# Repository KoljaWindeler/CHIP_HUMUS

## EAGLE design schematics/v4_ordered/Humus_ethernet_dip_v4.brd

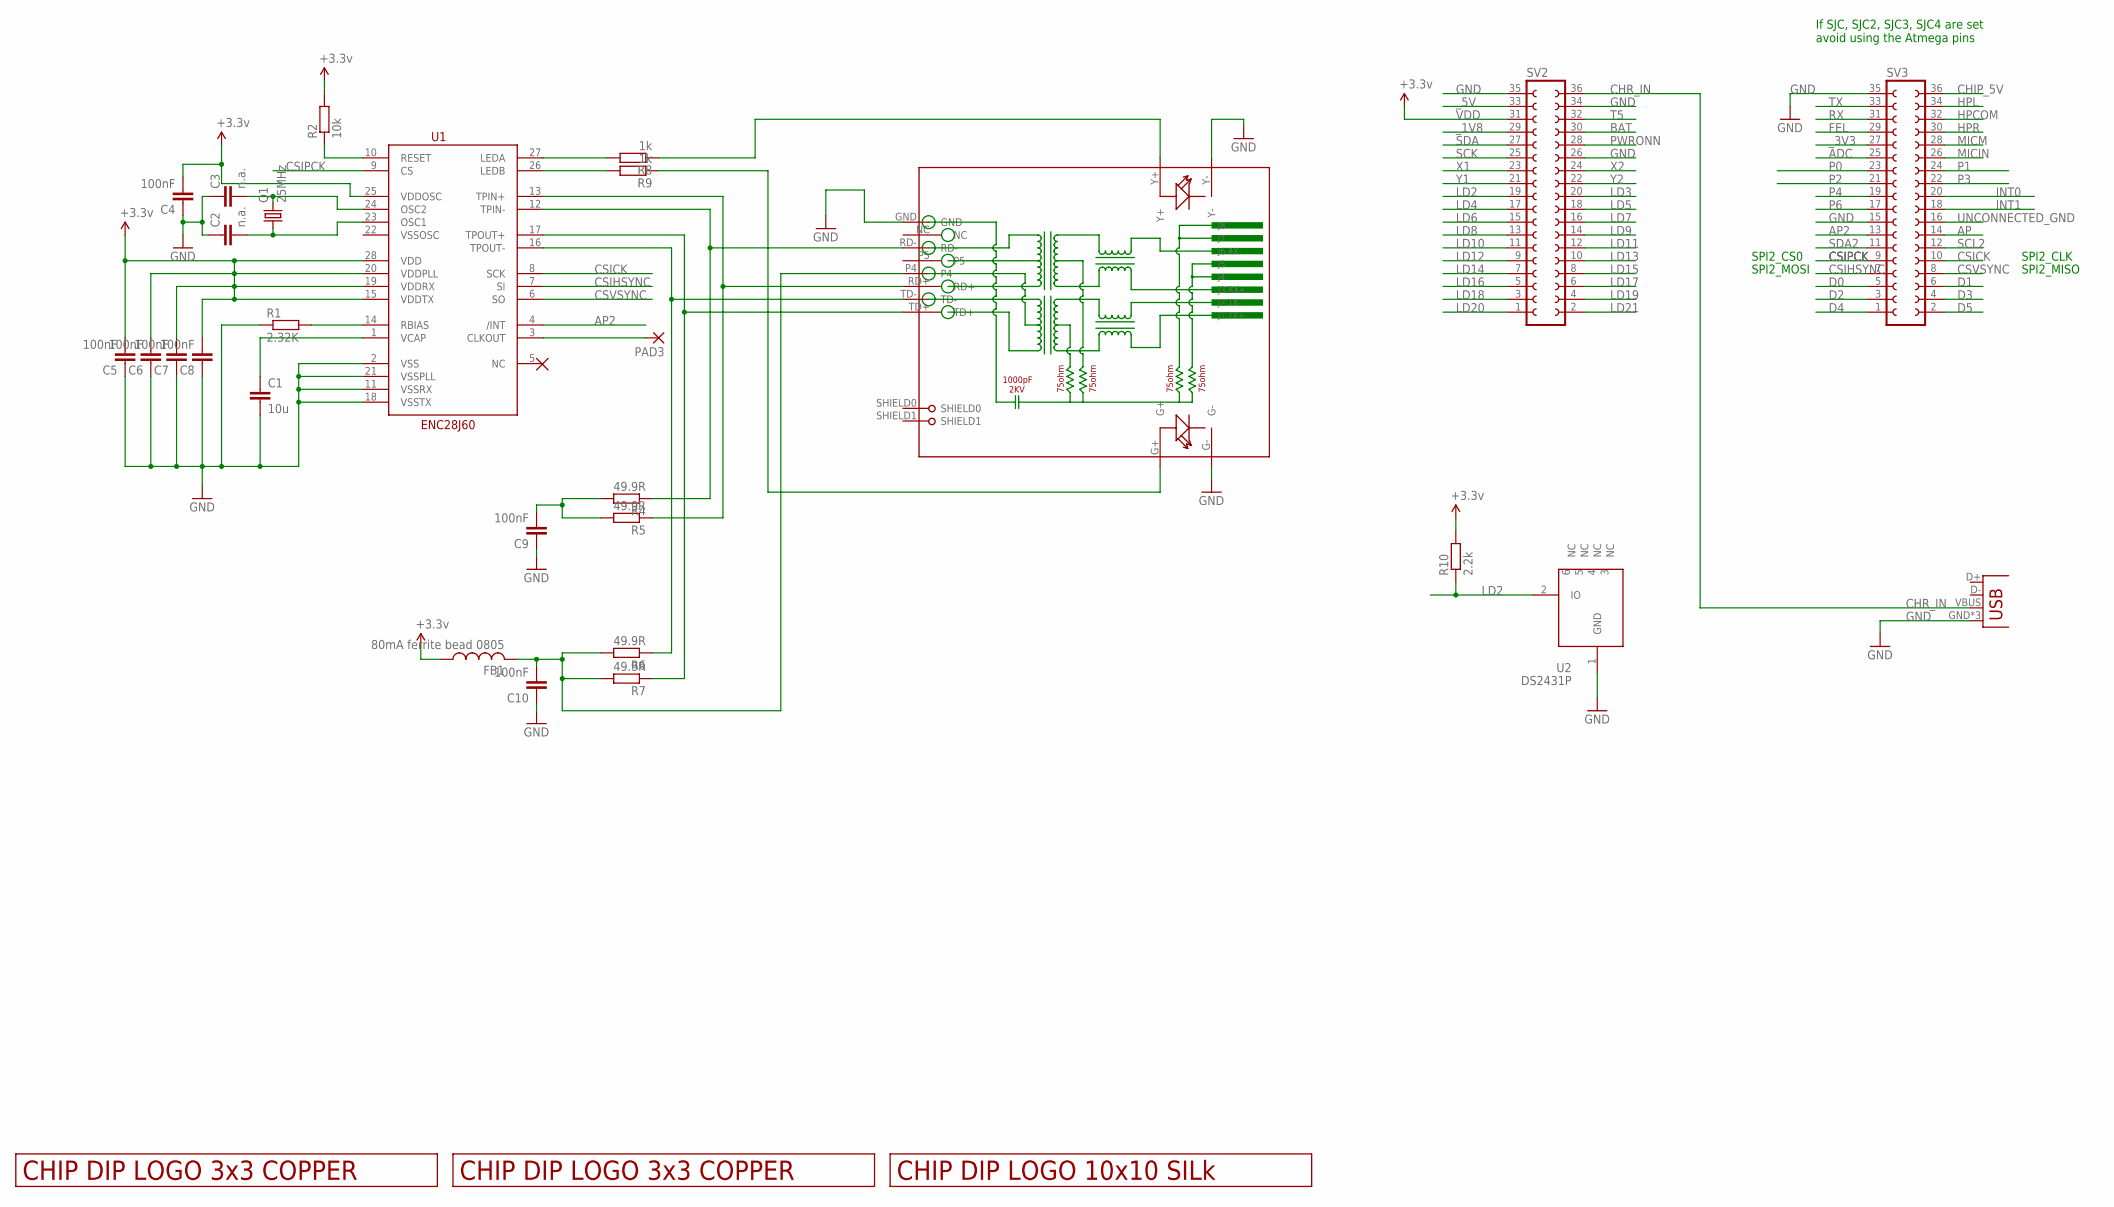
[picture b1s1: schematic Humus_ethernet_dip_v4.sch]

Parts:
C1: 10u; C0805
C2, C3: n.a.; C0805
C4, C5, C6, C7, C8, C9, C10: 100nF; C0805
FB1: 80mA ferrite bead 0805; 0805
PAD3: WIREPADSMD1,27-254; SMD1,27-2,54
Q1: 25MHz; SM49
R1: 2.32K; R0805
R2: 10k; R0805
R4, R5, R6, R7: 49.9R; R0805
R8, R9: 1k; R0805
R10: 2.2k; R0805
RJ1: HR911105A
SV2, SV3: FE18-2
U1: ENC28J60SS; SSOP28DB
U2: DS2431P; TSOC6
U$1: LOGO_10X10_SILK; LOGO2_10X10_SILK
U$2, U$4: LOGO_3X3_COPPER
USB: USBUSB-MICROB-SMT-DIP; USB-MICROB-SMT-DIP

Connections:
ADC: SV3.25
AP: SV3.14
AP2: SV3.13, U1.4 (/INT)
BAT: SV2.30
CHIP_5V: SV3.36
CHR_IN: SV2.36, USB.VBUS
CSICK: SV3.10, U1.8 (SCK)
CSIHSYNC: SV3.7, U1.7 (SI)
CSIPCK: SV3.9, U1.9 (CS)
CSVSYNC: SV3.8, U1.6 (SO)
CT: C10.2, FB1.2, R6.2, R7.2, RJ1.P4
D0: SV3.5
D1: SV3.6
D2: SV3.3
D3: SV3.4
D4: SV3.1
D5: SV3.2
FEL: SV3.29
GND: C1.2, C2.1, C3.1, C4.1, C5.1, C6.1, C7.1, C8.1, C9.1, C10.1, R1.1, RJ1.G-, RJ1.GND, RJ1.Y-, SV2.26, SV2.34, SV2.35, SV3.15, SV3.35, U1.2 (VSS), U1.11 (VSSRX), U1.18 (VSSTX), U1.21 (VSSPLL), U2.1 (GND), USB.GND, USB.MT1 (GND), USB.MT2 (GND)
HPCOM: SV3.32
HPL: SV3.34
HPR: SV3.30
INT0: SV3.20
INT1: SV3.18
LD2: R10.1, SV2.19, U2.2 (IO)
LD3: SV2.20
LD4: SV2.17
LD5: SV2.18
LD6: SV2.15
LD7: SV2.16
LD8: SV2.13
LD9: SV2.14
LD10: SV2.11
LD11: SV2.12
LD12: SV2.9
LD13: SV2.10
LD14: SV2.7
LD15: SV2.8
LD16: SV2.5
LD17: SV2.6
LD18: SV2.3
LD19: SV2.4
LD20: SV2.1
LD21: SV2.2
MICIN: SV3.26
MICM: SV3.28
unnamed: C1.1, U1.1 (VCAP)
unnamed: R2.1, U1.10 (RESET)
unnamed: R1.2, U1.14 (RBIAS)
unnamed: C3.2, Q1.2, U1.24 (OSC2)
unnamed: C2.2, Q1.1, U1.23 (OSC1)
unnamed: R8.1, RJ1.Y+
unnamed: R9.1, RJ1.G+
unnamed: PAD3.1, U1.3 (CLKOUT)
unnamed: C9.2, R4.2, R5.2
unnamed: R8.2, U1.27 (LEDA)
unnamed: R9.2, U1.26 (LEDB)
P0: SV3.23
P1: SV3.24
P2: SV3.21
P3: SV3.22
P4: SV3.19
P6: SV3.17
PWRONN: SV2.28
RD+: R5.1, RJ1.RD+, U1.13 (TPIN+)
RD-: R4.1, RJ1.RD-, U1.12 (TPIN-)
RX: SV3.31
SCK: SV2.25
SCL2: SV3.12
SDA: SV2.27
SDA2: SV3.11
T5: SV2.32
TD+: R7.1, RJ1.TD+, U1.17 (TPOUT+)
TD-: R6.1, RJ1.TD-, U1.16 (TPOUT-)
TX: SV3.33
UNCONNECTED_GND: SV3.16
VDD: C4.2, C5.2, C6.2, C7.2, C8.2, FB1.1, R2.2, R10.2, SV2.31, U1.15 (VDDTX), U1.19 (VDDRX), U1.20 (VDDPLL), U1.25 (VDDOSC), U1.28 (VDD)
X1: SV2.23
X2: SV2.24
Y1: SV2.21
Y2: SV2.22
_1V8: SV2.29
_3V3: SV3.27
_5V: SV2.33

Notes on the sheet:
If SJC, SJC2, SJC3, SJC4 are set avoid using the Atmega pins
SPI2_CS0
SPI2_CLK
SPI2_MOSI
SPI2_MISO

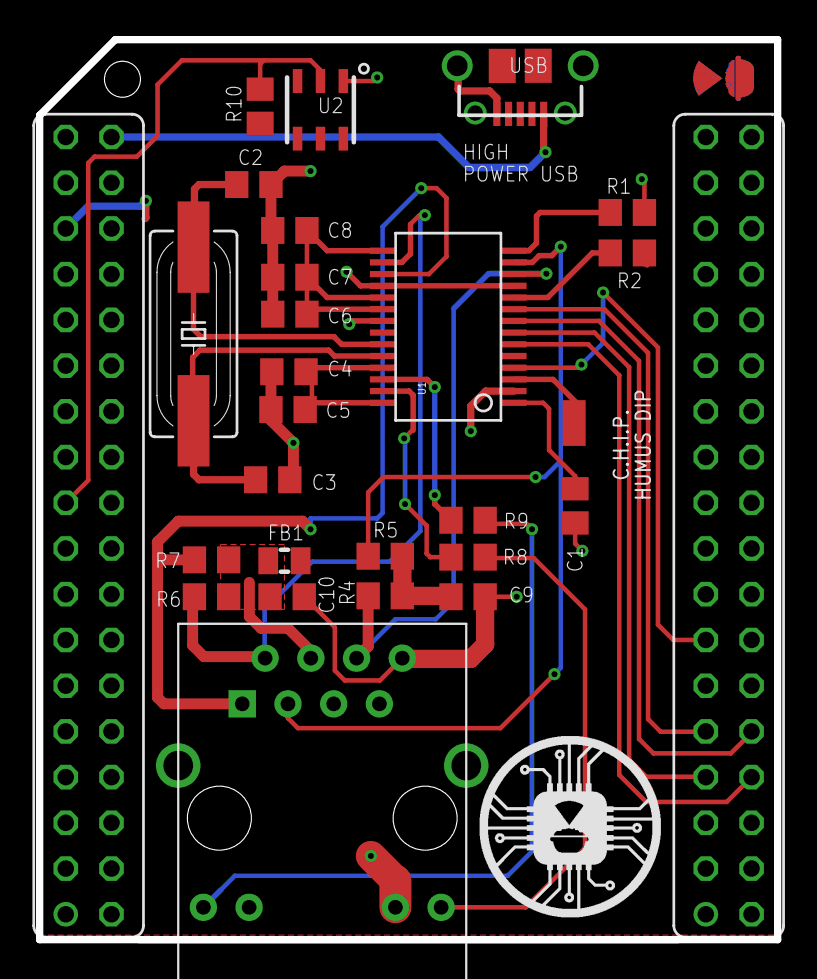
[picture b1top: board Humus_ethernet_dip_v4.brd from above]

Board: 2 copper layers, 41.0 x 50.0 mm, 31 parts (1 on the bottom side), 25 nets.

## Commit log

2016-04-07 :octocat: Added .gitattributes & .gitignore files
2016-04-07 init
2016-04-07 added eeprom
2016-04-07 routed interrupt pin
2016-04-07 improved layout and added artwork
2016-04-07 added artwork source
2016-04-17 added version two with EEPROM and DCDC
2016-04-17 added docu
2016-06-16 fixed connection
2016-06-16 added datasheet
2016-06-16 removed gerber
2016-06-16 rename to V2
2016-06-16 excluded backup files
2016-06-16 exclude gerber
2016-06-16 moved folder to v2_ordered
2016-06-20 Added version with jack on bottom
2016-06-20 gerber added
2016-07-10 added overlay
2016-07-14 added pins, still not working
2016-07-15 update dts
2016-07-17 working overlay, woop woop
2016-07-21 moved libs, dru, cam to common
2016-07-22 added quotation
2016-07-28 fixed ds2431
2016-07-28 updated quote
2016-07-29 new quote
2016-07-29 removed old quotes
2016-08-11 added load script
2016-08-11 removed dhclient from script
2016-08-17 added install early script
2016-08-17 reduced to one install file
2016-08-29 fixed install
2016-08-29 renamed folder v4 to ordered
2016-08-31 added desc
2016-10-14 added gerocortex mac assignment script
2016-11-20 added simple load
2016-11-20 use simple script by default
2016-11-20 added img
2016-11-22 Fixed filename

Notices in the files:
parts and their libraries:
SparkFun-DigitalIC: Licensing: Creative Commons ShareAlike 4.0 International - https://creativecommons.org/licenses/by-sa/4.0
m-pad-2.1: License : GNU General Public License version 2 (see bottom)
